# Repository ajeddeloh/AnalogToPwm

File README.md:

AnalogToPwm
===========

Converts analog voltage to PWM

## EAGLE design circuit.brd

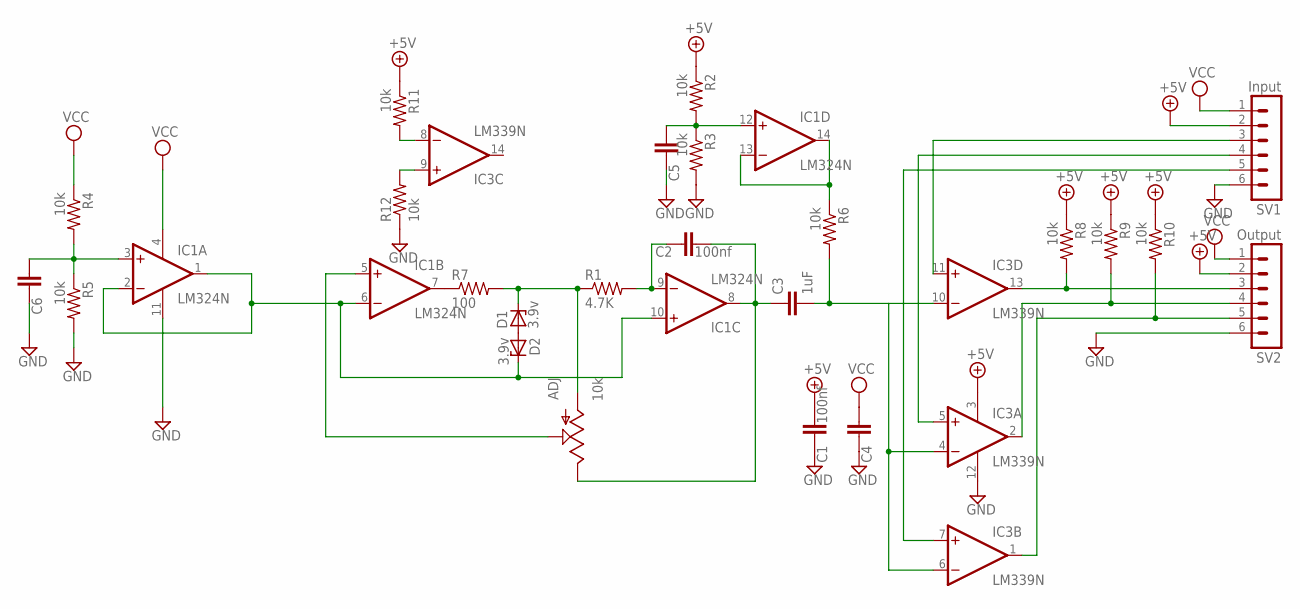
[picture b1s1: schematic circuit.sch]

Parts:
ADJ: 10k; TRIM_POT
C1, C2, C4, C5, C6: 100nf; C050-024X044
C3: 1uF; C050-035X075
D1, D2: 3.9v; DO41Z10
IC1: LM324N; DIL14
IC3: LM339N; DIL14
R1: 4.7K; 0207/12
R2, R3, R4, R5, R6, R9, R10, R11, R12: 10k; 0207/10
R7: 100; 0207/10
R8: 10k; 0207/7
SV1: Input; MA06-1
SV2: Output; MA06-1

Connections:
+5V: C1.2, IC3.3 (V+), R2.1, R8.1, R9.1, R10.1, R11.1, SV1.2, SV2.2
ARTGND: D2.C, IC1.1 (OUT), IC1.2 (-IN), IC1.6 (-IN), IC1.10 (+IN)
GND: C1.1, C4.1, C5.1, C6.1, IC1.11 (V-), IC3.12 (GND), R3.2, R5.2, R12.1, SV1.6, SV2.6
unnamed: ADJ.2 (E), C2.2, C3.1, IC1.8 (OUT)
unnamed: IC1.7 (OUT), R7.1
unnamed: D1.A, D2.A
unnamed: C2.1, IC1.9 (-IN), R1.2
unnamed: IC1.13 (-IN), IC1.14 (OUT), R6.1
unnamed: ADJ.3 (A), D1.C, R1.1, R7.2
unnamed: C6.2, IC1.3 (+IN), R4.2, R5.1
unnamed: ADJ.1 (S), IC1.5 (+IN)
unnamed: IC3.13 (OUT), R8.2, SV2.3
unnamed: IC3.2 (OUT), R9.2, SV2.4
unnamed: IC3.1 (OUT), R10.2, SV2.5
unnamed: IC3.11 (+IN), SV1.3
unnamed: IC3.5 (+IN), SV1.4
unnamed: IC3.7 (+IN), SV1.5
unnamed: C5.2, IC1.12 (+IN), R2.2, R3.1
unnamed: IC3.8 (-IN), R11.2
unnamed: IC3.9 (+IN), R12.2
unnamed: C3.2, IC3.4 (-IN), IC3.6 (-IN), IC3.10 (-IN), R6.2
VCC: C4.2, IC1.4 (V+), R4.1, SV1.1, SV2.1

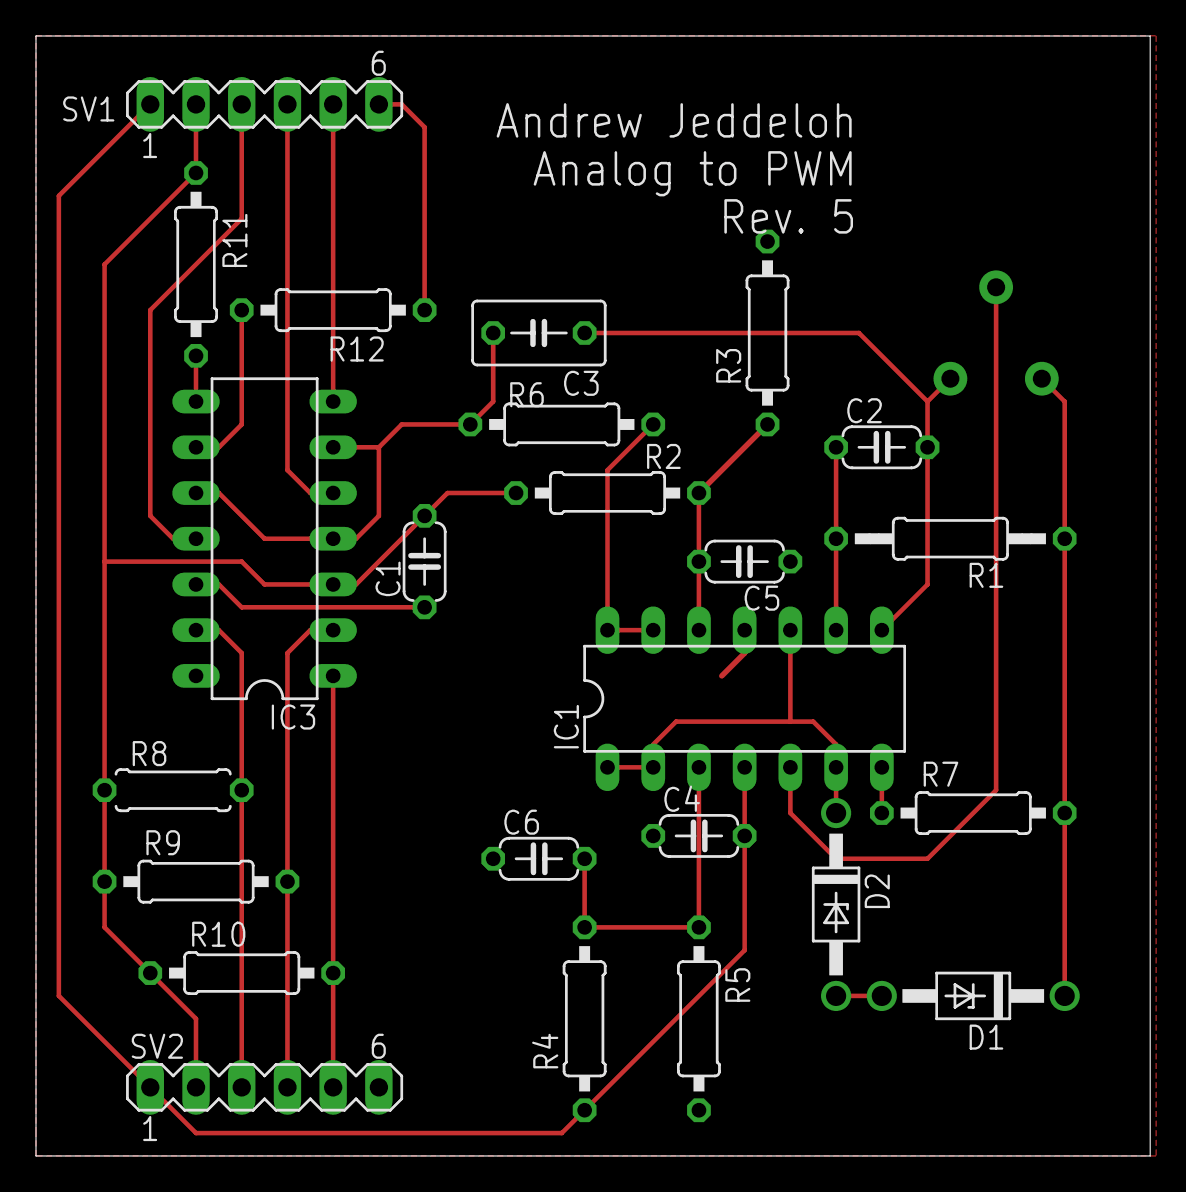
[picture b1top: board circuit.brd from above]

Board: 2 copper layers, 61.9 x 62.2 mm, 25 parts (0 on the bottom side), 22 nets.

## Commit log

2013-10-21 Uploading eagle files
2013-10-24 Updated to use comparator instead of op amps
2014-01-21 schematic: added decoupling caps for each IC as well as zener diodes so that the amplitude of the triangle wave is not dependent on supply voltage. Also added a trimpot to allow for triangle wave adj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

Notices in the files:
parts and their libraries:
SparkFun-Electromechanical: Licensing: CC v3.0 Share-Alike You are welcome to use this library for commercial purposes.
